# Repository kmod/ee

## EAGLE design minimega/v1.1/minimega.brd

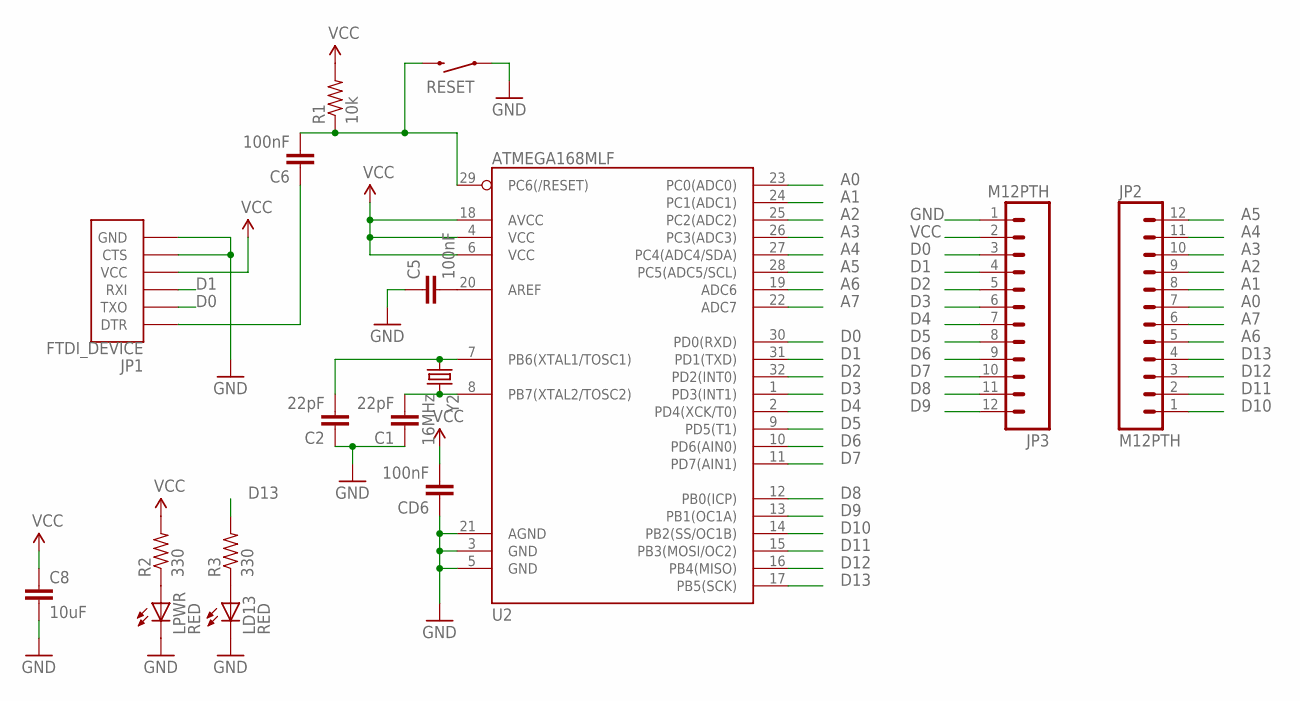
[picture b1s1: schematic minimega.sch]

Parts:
C1, C2: 22pF; 0402-CAP
C5, C6: 100nF; 0402-CAP
C8: 10uF; 0805
CD6: 100nF; 0402-CAP
JP1: FTDI_DEVICE; FTDI_DEVICE_SIDE
JP2, JP3: M12PTH; 1X12
LD13: RED; LED-0603
LPWR: RED; LED-0603
R1: 10k; 0603-RES
R2, R3: 330; 0603-RES
RESET: SWITCH-MOMENTARY-2PTH; TACTILE-PTH
U2: ATMEGA168MLF; MLF32
Y2: 16MHz; HC49UP

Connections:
A0: JP2.7, U2.23 (PC0(ADC0))
A1: JP2.8, U2.24 (PC1(ADC1))
A2: JP2.9, U2.25 (PC2(ADC2))
A3: JP2.10, U2.26 (PC3(ADC3))
A4: JP2.11, U2.27 (PC4(ADC4/SDA))
A5: JP2.12, U2.28 (PC5(ADC5/SCL))
A6: JP2.5, U2.19 (ADC6)
A7: JP2.6, U2.22 (ADC7)
D0: JP1.P$2 (TXO), JP3.3, U2.30 (PD0(RXD))
D1: JP1.P$3 (RXI), JP3.4, U2.31 (PD1(TXD))
D2: JP3.5, U2.32 (PD2(INT0))
D3: JP3.6, U2.1 (PD3(INT1))
D4: JP3.7, U2.2 (PD4(XCK/T0))
D5: JP3.8, U2.9 (PD5(T1))
D6: JP3.9, U2.10 (PD6(AIN0))
D7: JP3.10, U2.11 (PD7(AIN1))
D8: JP3.11, U2.12 (PB0(ICP))
D9: JP3.12, U2.13 (PB1(OC1A))
D10: JP2.1, U2.14 (PB2(SS/OC1B))
D11: JP2.2, U2.15 (PB3(MOSI/OC2))
D12: JP2.3, U2.16 (PB4(MISO))
D13: JP2.4, R3.2, U2.17 (PB5(SCK))
GND: C1.1, C2.1, C5.1, C8.2, CD6.1, JP1.P$5 (CTS), JP1.P$6 (GND), JP3.1, LD13.C, LPWR.C, RESET.1, U2.3 (GND), U2.5 (GND), U2.21 (AGND)
unnamed: LD13.A, R3.1
unnamed: C1.2, U2.8 (PB7(XTAL2/TOSC2)), Y2.2
unnamed: C2.2, U2.7 (PB6(XTAL1/TOSC1)), Y2.1
unnamed: C5.2, U2.20 (AREF)
unnamed: C6.2, R1.1, RESET.3 (2), U2.29 (PC6(/RESET))
unnamed: LPWR.A, R2.1
unnamed: C6.1, JP1.P$1 (DTR)
VCC: C8.1, CD6.2, JP1.P$4 (VCC), JP3.2, R1.2, R2.2, U2.4 (VCC), U2.6 (VCC), U2.18 (AVCC)

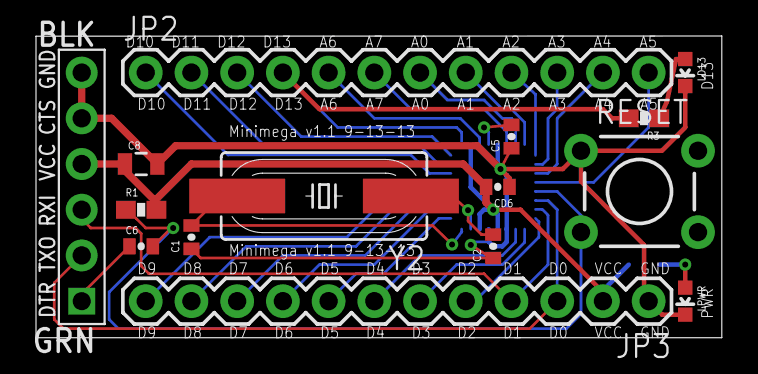
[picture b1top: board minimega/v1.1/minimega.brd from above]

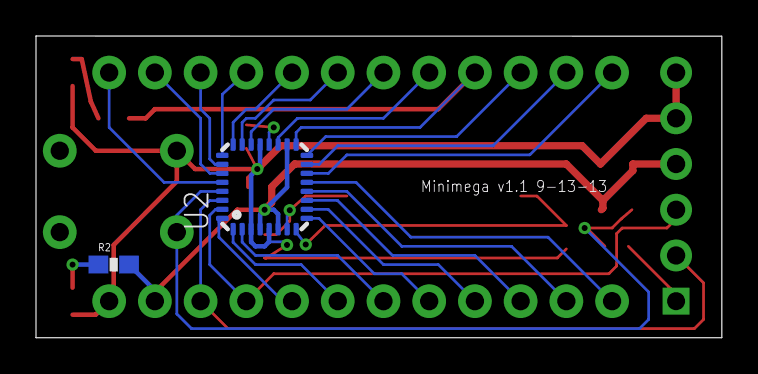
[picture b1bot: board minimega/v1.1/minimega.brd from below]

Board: 2 copper layers, 38.1 x 16.8 mm, 17 parts (2 on the bottom side), 31 nets.

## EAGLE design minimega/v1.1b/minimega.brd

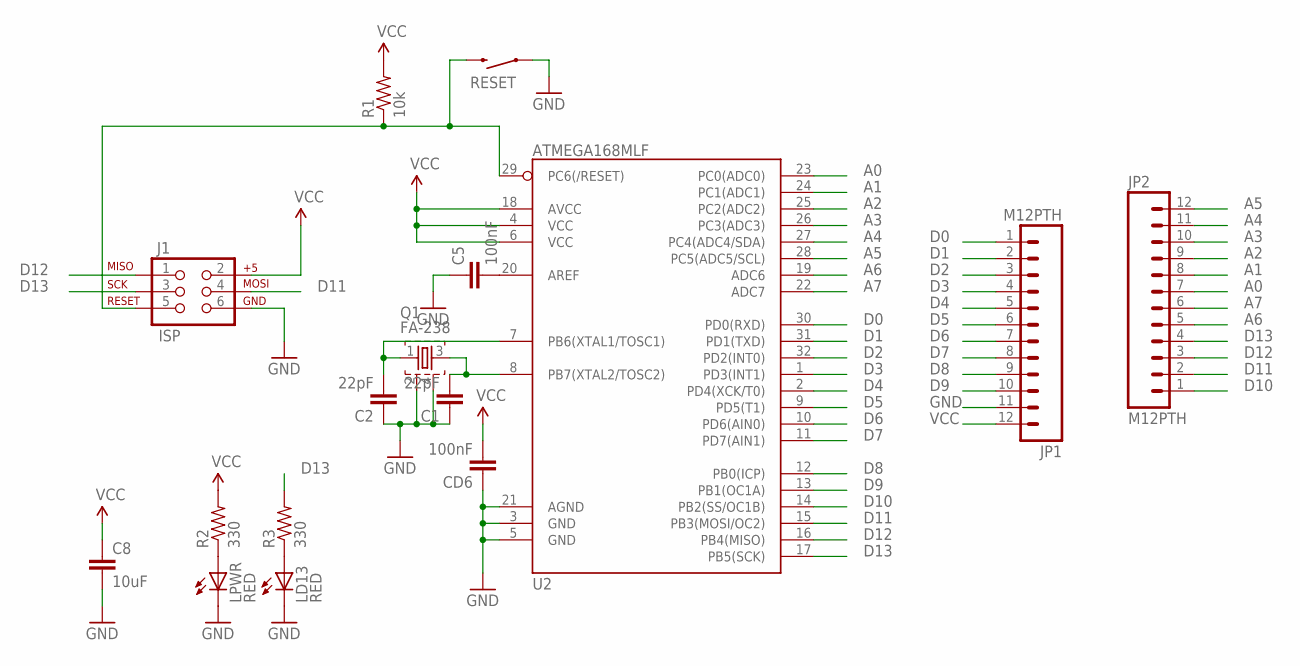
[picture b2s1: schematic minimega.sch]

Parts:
C1, C2: 22pF; 0402-CAP
C5: 100nF; 0402-CAP
C8: 10uF; 0805
CD6: 100nF; 0402-CAP
J1: ISP; 2X3
JP1, JP2: M12PTH; 1X12
LD13: RED; LED-0603
LPWR: RED; LED-0603
Q1: FA-238
R1: 10k; 0603-RES
R2, R3: 330; 0603-RES
RESET: SWITCH-MOMENTARY-2PTH; TACTILE-PTH
U2: ATMEGA168MLF; MLF32

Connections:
A0: JP2.7, U2.23 (PC0(ADC0))
A1: JP2.8, U2.24 (PC1(ADC1))
A2: JP2.9, U2.25 (PC2(ADC2))
A3: JP2.10, U2.26 (PC3(ADC3))
A4: JP2.11, U2.27 (PC4(ADC4/SDA))
A5: JP2.12, U2.28 (PC5(ADC5/SCL))
A6: JP2.5, U2.19 (ADC6)
A7: JP2.6, U2.22 (ADC7)
D0: JP1.1, U2.30 (PD0(RXD))
D1: JP1.2, U2.31 (PD1(TXD))
D2: JP1.3, U2.32 (PD2(INT0))
D3: JP1.4, U2.1 (PD3(INT1))
D4: JP1.5, U2.2 (PD4(XCK/T0))
D5: JP1.6, U2.9 (PD5(T1))
D6: JP1.7, U2.10 (PD6(AIN0))
D7: JP1.8, U2.11 (PD7(AIN1))
D8: JP1.9, U2.12 (PB0(ICP))
D9: JP1.10, U2.13 (PB1(OC1A))
D10: JP2.1, U2.14 (PB2(SS/OC1B))
D11: J1.4, JP2.2, U2.15 (PB3(MOSI/OC2))
D12: J1.1, JP2.3, U2.16 (PB4(MISO))
D13: J1.3, JP2.4, R3.2, U2.17 (PB5(SCK))
GND: C1.1, C2.1, C5.1, C8.2, CD6.1, J1.6, JP1.11, LD13.C, LPWR.C, Q1.2, Q1.4, RESET.1, U2.3 (GND), U2.5 (GND), U2.21 (AGND)
unnamed: LD13.A, R3.1
unnamed: C1.2, Q1.3, U2.8 (PB7(XTAL2/TOSC2))
unnamed: C2.2, Q1.1, U2.7 (PB6(XTAL1/TOSC1))
unnamed: C5.2, U2.20 (AREF)
unnamed: J1.5, R1.1, RESET.3 (2), U2.29 (PC6(/RESET))
unnamed: LPWR.A, R2.1
VCC: C8.1, CD6.2, J1.2, JP1.12, R1.2, R2.2, U2.4 (VCC), U2.6 (VCC), U2.18 (AVCC)

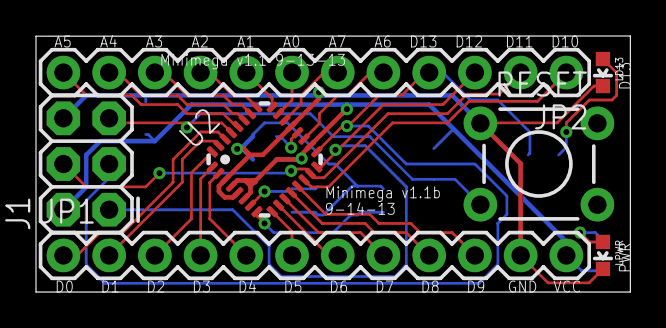
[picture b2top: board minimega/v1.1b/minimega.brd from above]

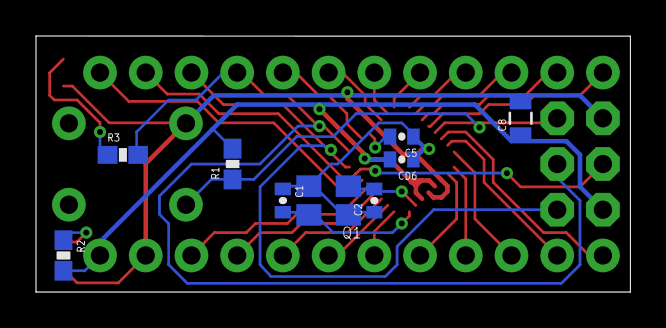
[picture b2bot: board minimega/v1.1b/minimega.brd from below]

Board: 2 copper layers, 33.0 x 14.2 mm, 16 parts (9 on the bottom side), 30 nets.

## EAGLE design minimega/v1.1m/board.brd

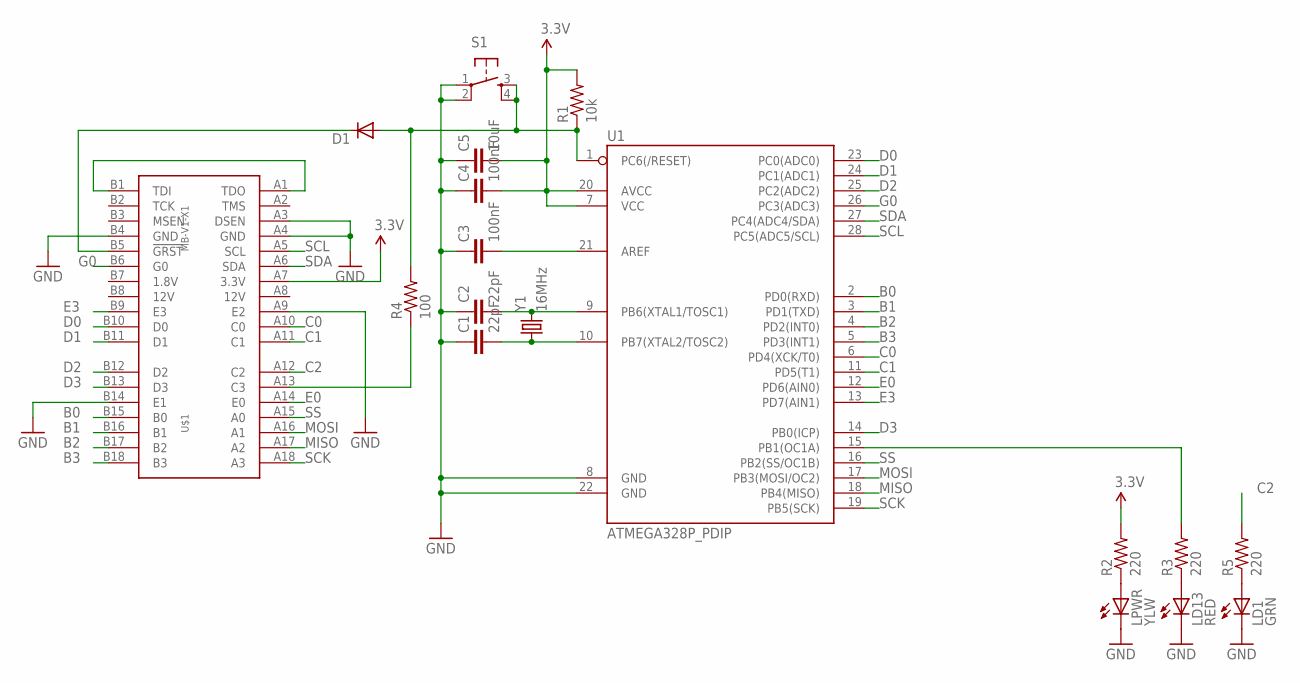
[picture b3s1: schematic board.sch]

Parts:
C1, C2: 22pF; 0402-CAP
C3, C4: 100nF; 0402-CAP
C5: 10uF; 0805
D1: DIODE1N4148; DIODE-1N4148
LD1: GRN; LED-0603
LD13: RED; LED-0603
LPWR: YLW; LED-0603
R1: 10k; 0603-RES
R2, R3, R5: 220; 0603-RES
R4: 100; 0603-RES
S1: TAC_SWITCHPTH; TACTILE-PTH
U1: ATMEGA328P_PDIP; DIL28-3
U$1: MB-V1-X1; PCIE-X1-EDGE
Y1: 16MHz; HC49US

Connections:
3.3V: C4.2, C5.2, R1.2, R2.2, U1.7 (VCC), U1.20 (AVCC), U$1.A7 (3.3V)
B0: U1.2 (PD0(RXD)), U$1.B15 (B0)
B1: U1.3 (PD1(TXD)), U$1.B16 (B1)
B2: U1.4 (PD2(INT0)), U$1.B17 (B2)
B3: U1.5 (PD3(INT1)), U$1.B18 (B3)
C0: U1.6 (PD4(XCK/T0)), U$1.A10 (C0)
C1: U1.11 (PD5(T1)), U$1.A11 (C1)
C2: R5.2, U$1.A12 (C2)
D0: U1.23 (PC0(ADC0)), U$1.B10 (D0)
D1: U1.24 (PC1(ADC1)), U$1.B11 (D1)
D2: U1.25 (PC2(ADC2)), U$1.B12 (D2)
D3: U1.14 (PB0(ICP)), U$1.B13 (D3)
E0: U1.12 (PD6(AIN0)), U$1.A14 (E0)
E3: U1.13 (PD7(AIN1)), U$1.B9 (E3)
G0: U1.26 (PC3(ADC3)), U$1.B6 (G0)
GND: C1.1, C2.1, C3.1, C4.1, C5.1, LD1.C, LD13.C, LPWR.C, S1.1, S1.2, U1.8 (GND), U1.22 (GND), U$1.A3 (DSEN), U$1.A4 (GND), U$1.A9 (E2), U$1.B4 (GND), U$1.B14 (E1)
MISO: U1.18 (PB4(MISO)), U$1.A17 (A2)
MOSI: U1.17 (PB3(MOSI/OC2)), U$1.A16 (A1)
unnamed: D1.C, U$1.B5 (!GRST)
unnamed: LD13.A, R3.1
unnamed: C2.2, U1.9 (PB6(XTAL1/TOSC1)), Y1.2
unnamed: C1.2, U1.10 (PB7(XTAL2/TOSC2)), Y1.1
unnamed: C3.2, U1.21 (AREF)
unnamed: U$1.A1 (TDO), U$1.B1 (TDI)
unnamed: LD1.A, R5.1
unnamed: R3.2, U1.15 (PB1(OC1A))
unnamed: R4.1, U$1.A13 (C3)
unnamed: LPWR.A, R2.1
RST: D1.A, R1.1, R4.2, S1.3, S1.4, U1.1 (PC6(/RESET))
SCK: U1.19 (PB5(SCK)), U$1.A18 (A3)
SCL: U1.28 (PC5(ADC5/SCL)), U$1.A5 (SCL)
SDA: U1.27 (PC4(ADC4/SDA)), U$1.A6 (SDA)
SS: U1.16 (PB2(SS/OC1B)), U$1.A15 (A0)

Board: 2 copper layers, 18 parts (0 on the bottom side), 33 nets, no tracks yet.

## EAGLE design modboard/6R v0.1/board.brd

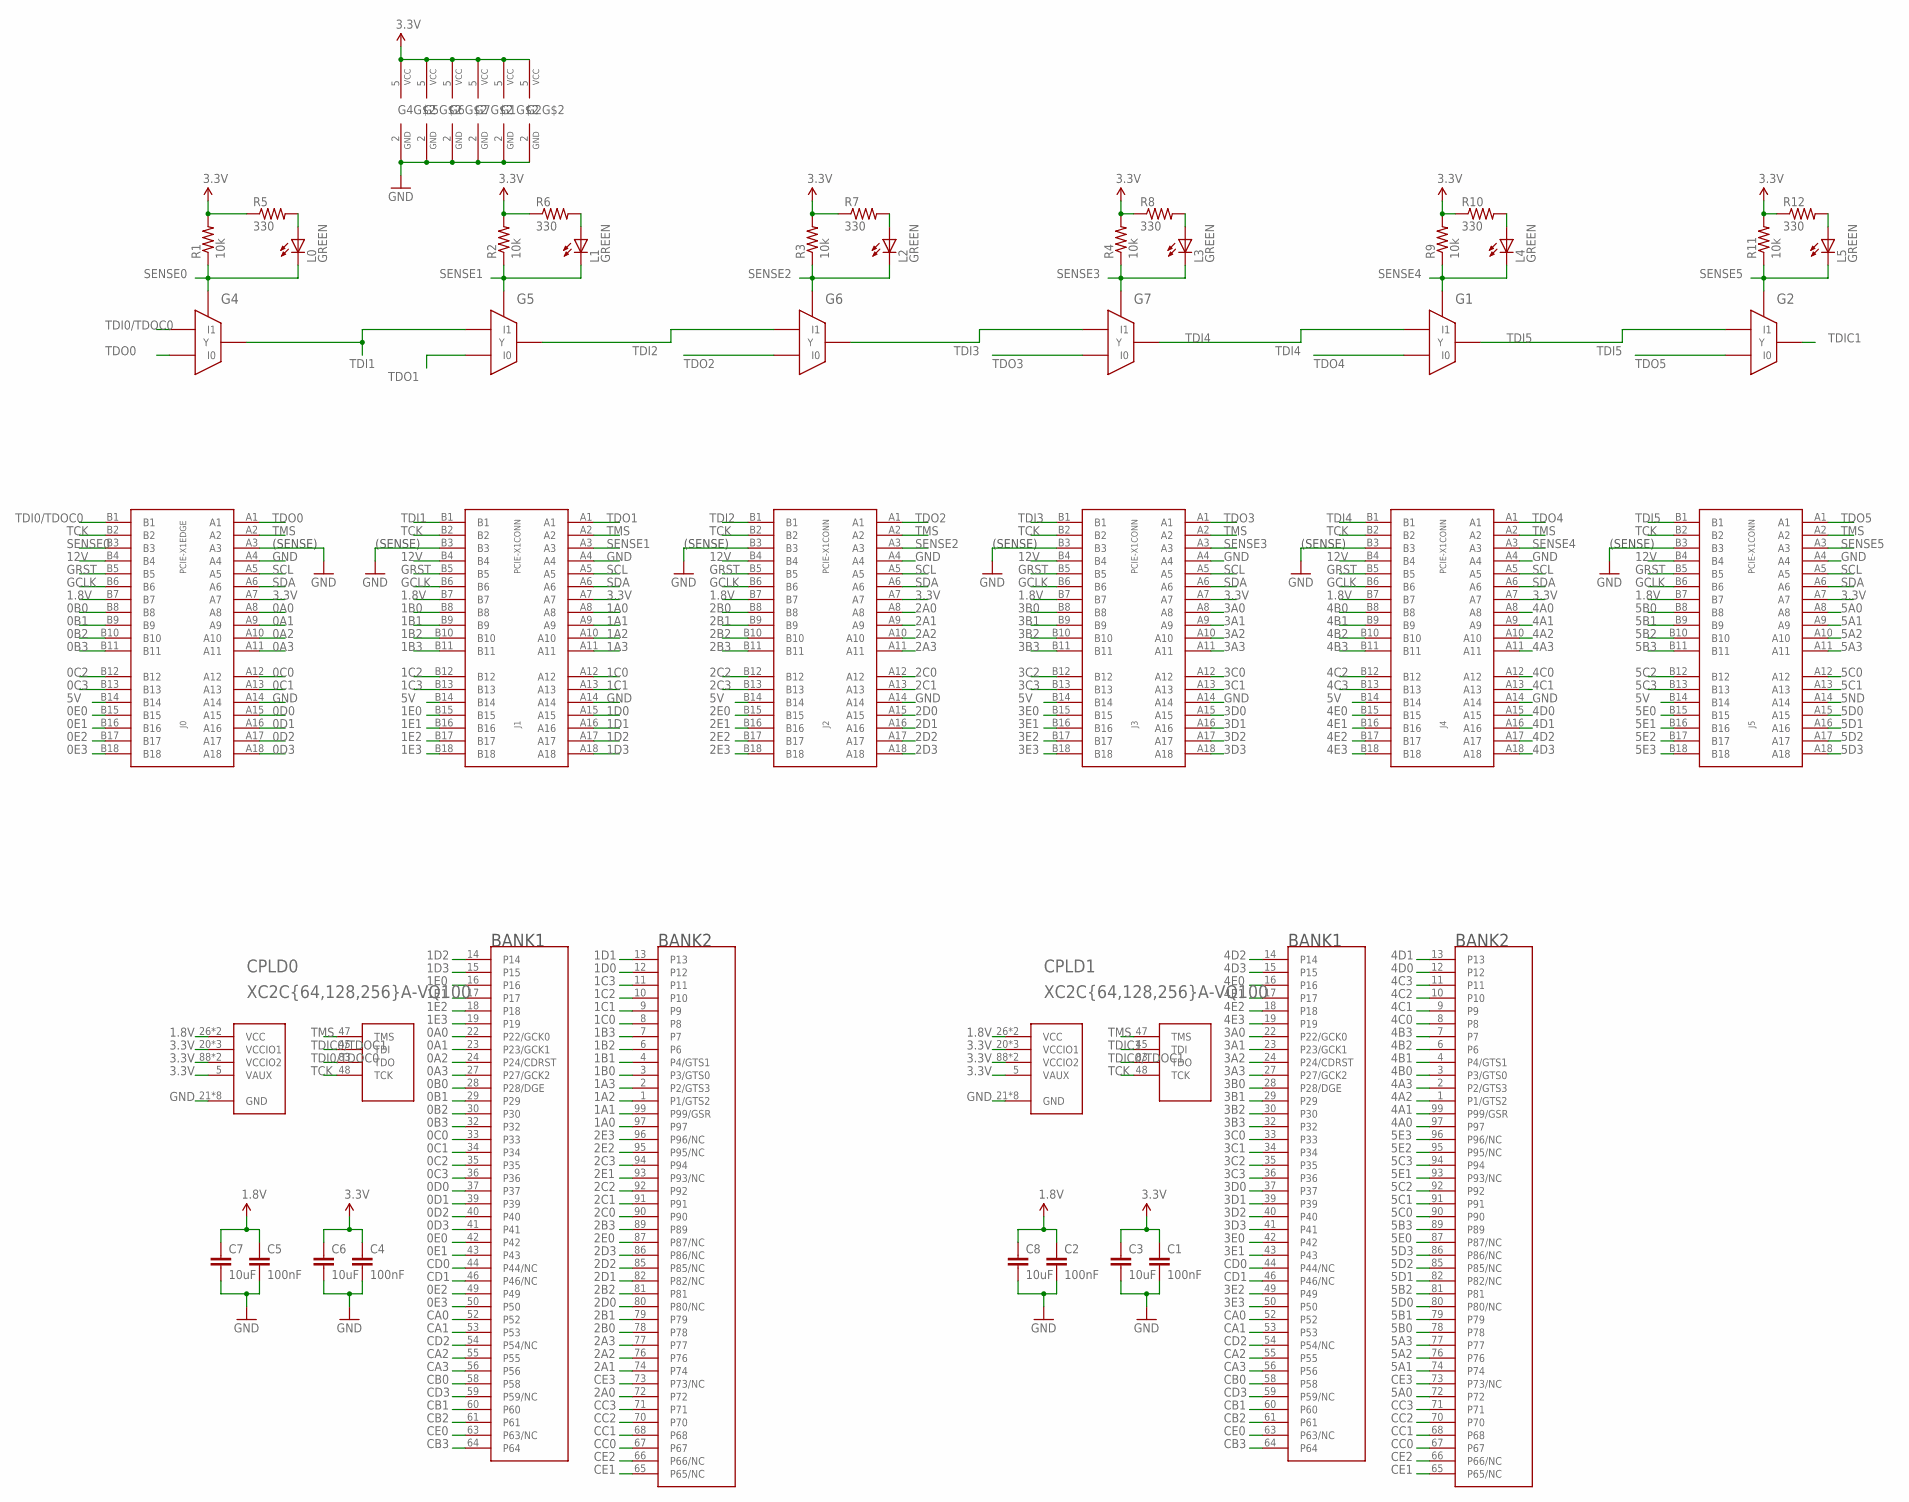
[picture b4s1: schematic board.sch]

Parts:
C1, C2, C4, C5: 100nF; 0402-CAP
C3, C6, C7, C8: 10uF; 0805
CPLD0, CPLD1: XC2C{64,128,256}A-VQ100; XILINX_TQ100
G1, G2, G4, G5, G6, G7: 74G157; SOT363
J0: PCIE-X1EDGE; PCIE-X1-EDGE
J1, J2, J3, J4, J5: PCIE-X1CONN; PCIE-X1-CONN
L0, L1, L2, L3, L4, L5: GREEN; 0603_LED
R1, R2, R3, R4, R9, R11: 10k; 0603-RES
R5, R6, R7, R8, R10, R12: 330; 0603-RES

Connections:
0A0: CPLD0.22 (P22/GCK0), J0.A8
0A1: CPLD0.23 (P23/GCK1), J0.A9
0A2: CPLD0.24 (P24/CDRST), J0.A10
0A3: CPLD0.27 (P27/GCK2), J0.A11
0B0: CPLD0.28 (P28/DGE), J0.B8
0B1: CPLD0.29, J0.B9
0B2: CPLD0.30, J0.B10
0B3: CPLD0.32, J0.B11
0C0: CPLD0.33, J0.A12
0C1: CPLD0.34, J0.A13
0C2: CPLD0.35, J0.B12
0C3: CPLD0.36, J0.B13
0D0: CPLD0.37, J0.A15
0D1: CPLD0.39, J0.A16
0D2: CPLD0.40, J0.A17
0D3: CPLD0.41, J0.A18
0E0: CPLD0.42, J0.B15
0E1: CPLD0.43, J0.B16
0E2: CPLD0.49, J0.B17
0E3: CPLD0.50, J0.B18
1.8V: C2.1, C5.1, C7.1, C8.1, CPLD0.26 (VCC), CPLD0.57 (VCC), CPLD1.26 (VCC), CPLD1.57 (VCC), J0.B7, J1.B7, J2.B7, J3.B7, J4.B7, J5.B7
1A0: CPLD0.97, J1.A8
1A1: CPLD0.99 (P99/GSR), J1.A9
1A2: CPLD0.1 (P1/GTS2), J1.A10
1A3: CPLD0.2 (P2/GTS3), J1.A11
1B0: CPLD0.3 (P3/GTS0), J1.B8
1B1: CPLD0.4 (P4/GTS1), J1.B9
1B2: CPLD0.6, J1.B10
1B3: CPLD0.7, J1.B11
1C0: CPLD0.8, J1.A12
1C1: CPLD0.9, J1.A13
1C2: CPLD0.10, J1.B12
1C3: CPLD0.11, J1.B13
1D0: CPLD0.12, J1.A15
1D1: CPLD0.13, J1.A16
1D2: CPLD0.14, J1.A17
1D3: CPLD0.15, J1.A18
1E0: CPLD0.16, J1.B15
1E1: CPLD0.17, J1.B16
1E2: CPLD0.18, J1.B17
1E3: CPLD0.19, J1.B18
2A0: CPLD0.72, J2.A8
2A1: CPLD0.74, J2.A9
2A2: CPLD0.76, J2.A10
2A3: CPLD0.77, J2.A11
2B0: CPLD0.78, J2.B8
2B1: CPLD0.79, J2.B9
2B2: CPLD0.81, J2.B10
2B3: CPLD0.89, J2.B11
2C0: CPLD0.90, J2.A12
2C1: CPLD0.91, J2.A13
2C2: CPLD0.92, J2.B12
2C3: CPLD0.94, J2.B13
2D0: CPLD0.80 (P80/NC), J2.A15
2D1: CPLD0.82 (P82/NC), J2.A16
2D2: CPLD0.85 (P85/NC), J2.A17
2D3: CPLD0.86 (P86/NC), J2.A18
2E0: CPLD0.87 (P87/NC), J2.B15
2E1: CPLD0.93 (P93/NC), J2.B16
2E2: CPLD0.95 (P95/NC), J2.B17
2E3: CPLD0.96 (P96/NC), J2.B18
3.3V: C1.1, C3.1, C4.1, C6.1, CPLD0.5 (VAUX), CPLD0.20 (VCCIO1), CPLD0.38 (VCCIO1), CPLD0.51 (VCCIO1), CPLD0.88 (VCCIO2), CPLD0.98 (VCCIO2), CPLD1.5 (VAUX), CPLD1.20 (VCCIO1), CPLD1.38 (VCCIO1), CPLD1.51 (VCCIO1), CPLD1.88 (VCCIO2), CPLD1.98 (VCCIO2), G1.5 (VCC), G2.5 (VCC), G4.5 (VCC), G5.5 (VCC), G6.5 (VCC), G7.5 (VCC), J0.A7, J1.A7, J2.A7, J3.A7, J4.A7, J5.A7, R1.2, R2.2, R3.2, R4.2, R5.1, R6.1, R7.1, R8.1, R9.2, R10.1, R11.2, R12.1
3A0: CPLD1.22 (P22/GCK0), J3.A8
3A1: CPLD1.23 (P23/GCK1), J3.A9
3A2: CPLD1.24 (P24/CDRST), J3.A10
3A3: CPLD1.27 (P27/GCK2), J3.A11
3B0: CPLD1.28 (P28/DGE), J3.B8
3B1: CPLD1.29, J3.B9
3B2: CPLD1.30, J3.B10
3B3: CPLD1.32, J3.B11
3C0: CPLD1.33, J3.A12
3C1: CPLD1.34, J3.A13
3C2: CPLD1.35, J3.B12
3C3: CPLD1.36, J3.B13
3D0: CPLD1.37, J3.A15
3D1: CPLD1.39, J3.A16
3D2: CPLD1.40, J3.A17
3D3: CPLD1.41, J3.A18
3E0: CPLD1.42, J3.B15
3E1: CPLD1.43, J3.B16
3E2: CPLD1.49, J3.B17
3E3: CPLD1.50, J3.B18
4A0: CPLD1.97, J4.A8
4A1: CPLD1.99 (P99/GSR), J4.A9
4A2: CPLD1.1 (P1/GTS2), J4.A10
4A3: CPLD1.2 (P2/GTS3), J4.A11
4B0: CPLD1.3 (P3/GTS0), J4.B8
4B1: CPLD1.4 (P4/GTS1), J4.B9
4B2: CPLD1.6, J4.B10
4B3: CPLD1.7, J4.B11
4C0: CPLD1.8, J4.A12
4C1: CPLD1.9, J4.A13
4C2: CPLD1.10, J4.B12
4C3: CPLD1.11, J4.B13
4D0: CPLD1.12, J4.A15
4D1: CPLD1.13, J4.A16
4D2: CPLD1.14, J4.A17
4D3: CPLD1.15, J4.A18
4E0: CPLD1.16, J4.B15
4E1: CPLD1.17, J4.B16
4E2: CPLD1.18, J4.B17
4E3: CPLD1.19, J4.B18
5A0: CPLD1.72, J5.A8
5A1: CPLD1.74, J5.A9
5A2: CPLD1.76, J5.A10
5A3: CPLD1.77, J5.A11
5B0: CPLD1.78, J5.B8
5B1: CPLD1.79, J5.B9
5B2: CPLD1.81, J5.B10
5B3: CPLD1.89, J5.B11
5C0: CPLD1.90, J5.A12
5C1: CPLD1.91, J5.A13
5C2: CPLD1.92, J5.B12
5C3: CPLD1.94, J5.B13
5D0: CPLD1.80 (P80/NC), J5.A15
5D1: CPLD1.82 (P82/NC), J5.A16
5D2: CPLD1.85 (P85/NC), J5.A17
5D3: CPLD1.86 (P86/NC), J5.A18
5E0: CPLD1.87 (P87/NC), J5.B15
5E1: CPLD1.93 (P93/NC), J5.B16
5E2: CPLD1.95 (P95/NC), J5.B17
5E3: CPLD1.96 (P96/NC), J5.B18
5ND: J5.A14
5V: J0.B14, J1.B14, J2.B14, J3.B14, J4.B14, J5.B14
12V: J0.B4, J1.B4, J2.B4, J3.B4, J4.B4, J5.B4
CA0: CPLD0.52, CPLD1.52
CA1: CPLD0.53, CPLD1.53
CA2: CPLD0.55, CPLD1.55
CA3: CPLD0.56, CPLD1.56
CB0: CPLD0.58, CPLD1.58
CB1: CPLD0.60, CPLD1.60
CB2: CPLD0.61, CPLD1.61
CB3: CPLD0.64, CPLD1.64
CC0: CPLD0.67, CPLD1.67
CC1: CPLD0.68, CPLD1.68
CC2: CPLD0.70, CPLD1.70
CC3: CPLD0.71, CPLD1.71
CD0: CPLD0.44 (P44/NC), CPLD1.44 (P44/NC)
CD1: CPLD0.46 (P46/NC), CPLD1.46 (P46/NC)
CD2: CPLD0.54 (P54/NC), CPLD1.54 (P54/NC)
CD3: CPLD0.59 (P59/NC), CPLD1.59 (P59/NC)
CE0: CPLD0.63 (P63/NC), CPLD1.63 (P63/NC)
CE1: CPLD0.65 (P65/NC), CPLD1.65 (P65/NC)
CE2: CPLD0.66 (P66/NC), CPLD1.66 (P66/NC)
CE3: CPLD0.73 (P73/NC), CPLD1.73 (P73/NC)
GCLK: J0.B6, J1.B6, J2.B6, J3.B6, J4.B6, J5.B6
GND: C1.2, C2.2, C3.2, C4.2, C5.2, C6.2, C7.2, C8.2, CPLD0.21 (GND), CPLD0.25 (GND), CPLD0.31 (GND), CPLD0.62 (GND), CPLD0.69 (GND), CPLD0.75 (GND), CPLD0.84 (GND), CPLD0.100 (GND), CPLD1.21 (GND), CPLD1.25 (GND), CPLD1.31 (GND), CPLD1.62 (GND), CPLD1.69 (GND), CPLD1.75 (GND), CPLD1.84 (GND), CPLD1.100 (GND), G1.2 (GND), G2.2 (GND), G4.2 (GND), G5.2 (GND), G6.2 (GND), G7.2 (GND), J0.A3, J0.A4, J0.A14, J1.A4, J1.A14, J1.B3, J2.A4, J2.A14, J2.B3, J3.A4, J3.A14, J3.B3, J4.A4, J4.A14, J4.B3, J5.A4, J5.B3
GRST: J0.B5, J1.B5, J2.B5, J3.B5, J4.B5, J5.B5
unnamed: L4.A, R10.2
unnamed: L5.A, R12.2
unnamed: L0.A, R5.2
unnamed: L1.A, R6.2
unnamed: L2.A, R7.2
unnamed: L3.A, R8.2
SCL: J0.A5, J1.A5, J2.A5, J3.A5, J4.A5, J5.A5
SDA: J0.A6, J1.A6, J2.A6, J3.A6, J4.A6, J5.A6
SENSE0: G4.6 (S), J0.B3, L0.C, R1.1
SENSE1: G5.6 (S), J1.A3, L1.C, R2.1
SENSE2: G6.6 (S), J2.A3, L2.C, R3.1
SENSE3: G7.6 (S), J3.A3, L3.C, R4.1
SENSE4: G1.6 (S), J4.A3, L4.C, R9.1
SENSE5: G2.6 (S), J5.A3, L5.C, R11.1
TCK: CPLD0.48 (TCK), CPLD1.48 (TCK), J0.B2, J1.B2, J2.B2, J3.B2, J4.B2, J5.B2
TDI0/TDOC0: CPLD0.83 (TDO), G4.1 (I1), J0.B1
TDI1: G4.4 (Y), G5.1 (I1), J1.B1
TDI2: G5.4 (Y), G6.1 (I1), J2.B1
TDI3: G6.4 (Y), G7.1 (I1), J3.B1
TDI4: G1.1 (I1), G7.4 (Y), J4.B1
TDI5: G1.4 (Y), G2.1 (I1), J5.B1
TDIC0/TDOC1: CPLD0.45 (TDI), CPLD1.83 (TDO)
TDIC1: CPLD1.45 (TDI), G2.4 (Y)
TDO0: G4.3 (I0), J0.A1
TDO1: G5.3 (I0), J1.A1
TDO2: G6.3 (I0), J2.A1
TDO3: G7.3 (I0), J3.A1
TDO4: G1.3 (I0), J4.A1
TDO5: G2.3 (I0), J5.A1
TMS: CPLD0.47 (TMS), CPLD1.47 (TMS), J0.A2, J1.A2, J2.A2, J3.A2, J4.A2, J5.A2

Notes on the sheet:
(SENSE)

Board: 2 copper layers, 40 parts (0 on the bottom side), 177 nets, no tracks yet.

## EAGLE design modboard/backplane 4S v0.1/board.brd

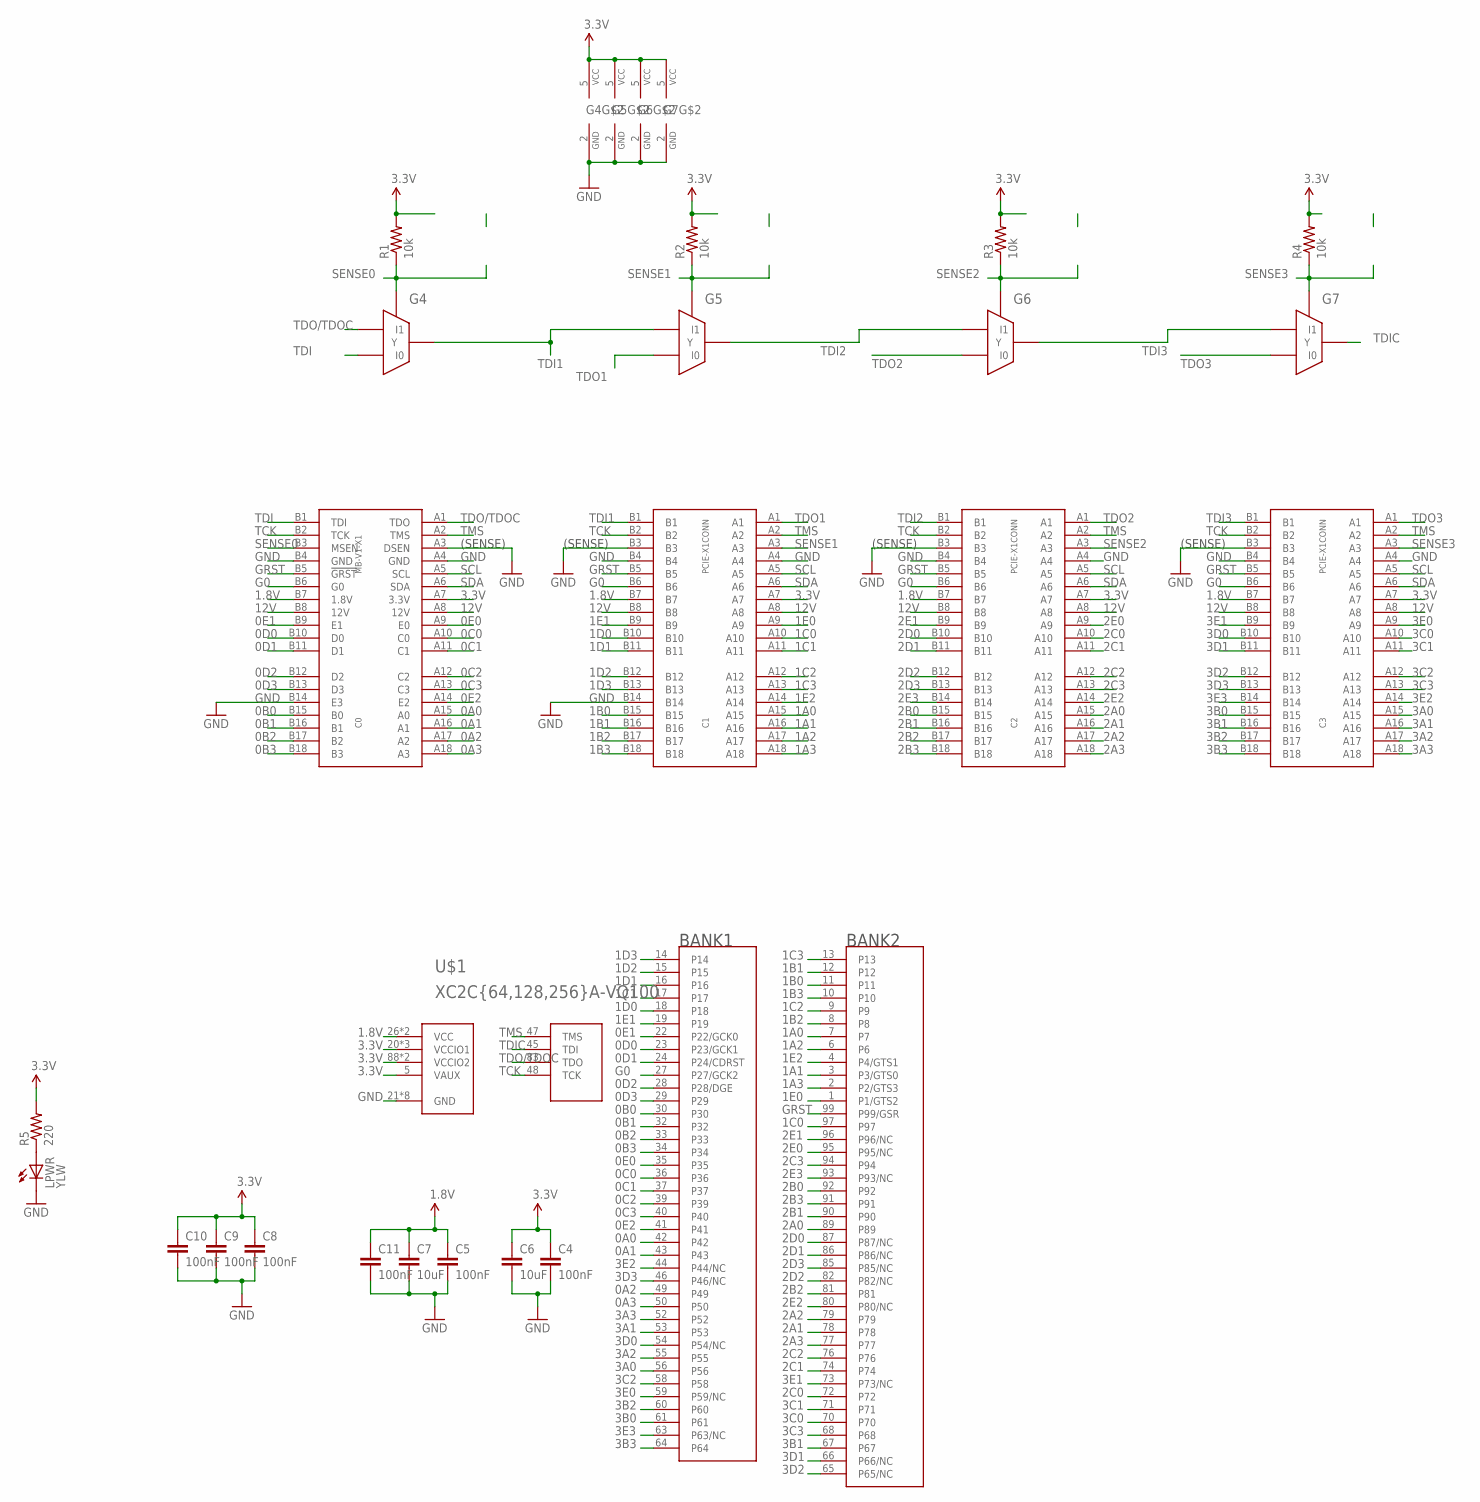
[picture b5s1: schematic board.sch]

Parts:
C0: MB-V1-X1; PCIE-X1-EDGE
C1, C2, C3: PCIE-X1CONN; PCIE-X1-CONN
C4, C5, C8, C9, C10, C11: 100nF; 0402-CAP
C6, C7: 10uF; 0805
G4, G5, G6, G7: 74G157; SOT363
LPWR: YLW; LED-0603
R1, R2, R3, R4: 10k; 0603-RES
R5: 220; 0603-RES
U$1: XC2C{64,128,256}A-VQ100; XILINX_TQ100

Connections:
0A0: C0.A15 (A0), U$1.42
0A1: C0.A16 (A1), U$1.43
0A2: C0.A17 (A2), U$1.49
0A3: C0.A18 (A3), U$1.50
0B0: C0.B15 (B0), U$1.30
0B1: C0.B16 (B1), U$1.32
0B2: C0.B17 (B2), U$1.33
0B3: C0.B18 (B3), U$1.34
0C0: C0.A10 (C0), U$1.36
0C1: C0.A11 (C1), U$1.37
0C2: C0.A12 (C2), U$1.39
0C3: C0.A13 (C3), U$1.40
0D0: C0.B10 (D0), U$1.23 (P23/GCK1)
0D1: C0.B11 (D1), U$1.24 (P24/CDRST)
0D2: C0.B12 (D2), U$1.28 (P28/DGE)
0D3: C0.B13 (D3), U$1.29
0E0: C0.A9 (E0), U$1.35
0E1: C0.B9 (E1), U$1.22 (P22/GCK0)
0E2: C0.A14 (E2), U$1.41
1.8V: C0.B7 (1.8V), C1.B7, C2.B7, C3.B7, C5.1, C7.1, C11.1, U$1.26 (VCC), U$1.57 (VCC)
1A0: C1.A15, U$1.7
1A1: C1.A16, U$1.3 (P3/GTS0)
1A2: C1.A17, U$1.6
1A3: C1.A18, U$1.2 (P2/GTS3)
1B0: C1.B15, U$1.11
1B1: C1.B16, U$1.12
1B2: C1.B17, U$1.8
1B3: C1.B18, U$1.10
1C0: C1.A10, U$1.97
1C1: C1.A11, U$1.17
1C2: C1.A12, U$1.9
1C3: C1.A13, U$1.13
1D0: C1.B10, U$1.18
1D1: C1.B11, U$1.16
1D2: C1.B12, U$1.15
1D3: C1.B13, U$1.14
1E0: C1.A9, U$1.1 (P1/GTS2)
1E1: C1.B9, U$1.19
1E2: C1.A14, U$1.4 (P4/GTS1)
2A0: C2.A15, U$1.89
2A1: C2.A16, U$1.78
2A2: C2.A17, U$1.79
2A3: C2.A18, U$1.77
2B0: C2.B15, U$1.92
2B1: C2.B16, U$1.90
2B2: C2.B17, U$1.81
2B3: C2.B18, U$1.91
2C0: C2.A10, U$1.72
2C1: C2.A11, U$1.74
2C2: C2.A12, U$1.76
2C3: C2.A13, U$1.94
2D0: C2.B10, U$1.87 (P87/NC)
2D1: C2.B11, U$1.86 (P86/NC)
2D2: C2.B12, U$1.82 (P82/NC)
2D3: C2.B13, U$1.85 (P85/NC)
2E0: C2.A9, U$1.95 (P95/NC)
2E1: C2.B9, U$1.96 (P96/NC)
2E2: C2.A14, U$1.80 (P80/NC)
2E3: C2.B14, U$1.93 (P93/NC)
3.3V: C0.A7 (3.3V), C1.A7, C2.A7, C3.A7, C4.1, C6.1, C8.1, C9.1, C10.1, G4.5 (VCC), G5.5 (VCC), G6.5 (VCC), G7.5 (VCC), R1.2, R2.2, R3.2, R4.2, R5.2, U$1.5 (VAUX), U$1.20 (VCCIO1), U$1.38 (VCCIO1), U$1.51 (VCCIO1), U$1.88 (VCCIO2), U$1.98 (VCCIO2)
3A0: C3.A15, U$1.56
3A1: C3.A16, U$1.53
3A2: C3.A17, U$1.55
3A3: C3.A18, U$1.52
3B0: C3.B15, U$1.61
3B1: C3.B16, U$1.67
3B2: C3.B17, U$1.60
3B3: C3.B18, U$1.64
3C0: C3.A10, U$1.70
3C1: C3.A11, U$1.71
3C2: C3.A12, U$1.58
3C3: C3.A13, U$1.68
3D0: C3.B10, U$1.54 (P54/NC)
3D1: C3.B11, U$1.66 (P66/NC)
3D2: C3.B12, U$1.65 (P65/NC)
3D3: C3.B13, U$1.46 (P46/NC)
3E0: C3.A9, U$1.59 (P59/NC)
3E1: C3.B9, U$1.73 (P73/NC)
3E2: C3.A14, U$1.44 (P44/NC)
3E3: C3.B14, U$1.63 (P63/NC)
12V: C0.A8 (12V), C0.B8 (12V), C1.A8, C1.B8, C2.A8, C2.B8, C3.A8, C3.B8
G0: C0.B6 (G0), C1.B6, C2.B6, C3.B6, U$1.27 (P27/GCK2)
GND: C0.A3 (DSEN), C0.A4 (GND), C0.B4 (GND), C0.B14 (E3), C1.A4, C1.B3, C1.B4, C1.B14, C2.A4, C2.B3, C2.B4, C3.A4, C3.B3, C3.B4, C4.2, C5.2, C6.2, C7.2, C8.2, C9.2, C10.2, C11.2, G4.2 (GND), G5.2 (GND), G6.2 (GND), G7.2 (GND), LPWR.C, U$1.21 (GND), U$1.25 (GND), U$1.31 (GND), U$1.62 (GND), U$1.69 (GND), U$1.75 (GND), U$1.84 (GND), U$1.100 (GND)
GRST: C0.B5 (!GRST), C1.B5, C2.B5, C3.B5, U$1.99 (P99/GSR)
unnamed: LPWR.A, R5.1
SCL: C0.A5 (SCL), C1.A5, C2.A5, C3.A5
SDA: C0.A6 (SDA), C1.A6, C2.A6, C3.A6
SENSE0: C0.B3 (MSEN), G4.6 (S), R1.1
SENSE1: C1.A3, G5.6 (S), R2.1
SENSE2: C2.A3, G6.6 (S), R3.1
SENSE3: C3.A3, G7.6 (S), R4.1
TCK: C0.B2 (TCK), C1.B2, C2.B2, C3.B2, U$1.48 (TCK)
TDI: C0.B1 (TDI), G4.3 (I0)
TDI1: C1.B1, G4.4 (Y), G5.1 (I1)
TDI2: C2.B1, G5.4 (Y), G6.1 (I1)
TDI3: C3.B1, G6.4 (Y), G7.1 (I1)
TDIC: G7.4 (Y), U$1.45 (TDI)
TDO1: C1.A1, G5.3 (I0)
TDO2: C2.A1, G6.3 (I0)
TDO3: C3.A1, G7.3 (I0)
TDO/TDOC: C0.A1 (TDO), G4.1 (I1), U$1.83 (TDO)
TMS: C0.A2 (TMS), C1.A2, C2.A2, C3.A2, U$1.47 (TMS)

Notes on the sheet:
(SENSE)

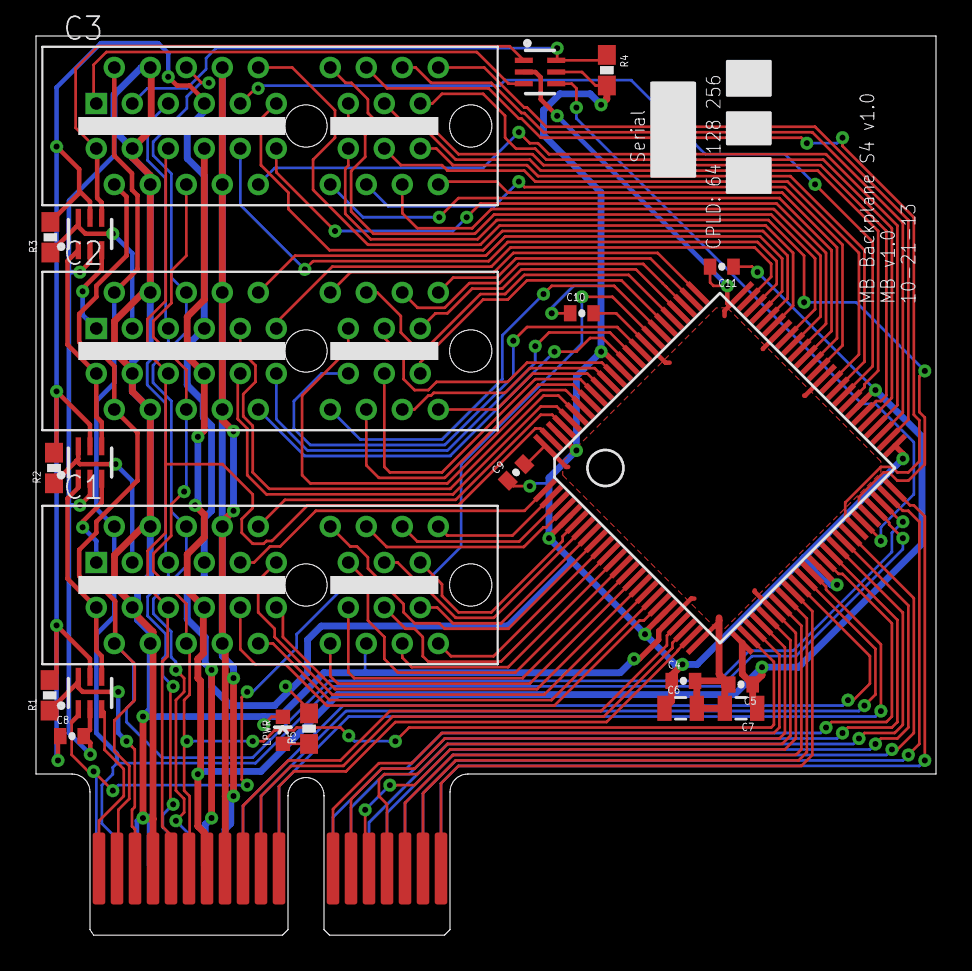
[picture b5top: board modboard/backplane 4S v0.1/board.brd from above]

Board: 2 copper layers, 50.0 x 50.0 mm, 23 parts (0 on the bottom side), 102 nets.

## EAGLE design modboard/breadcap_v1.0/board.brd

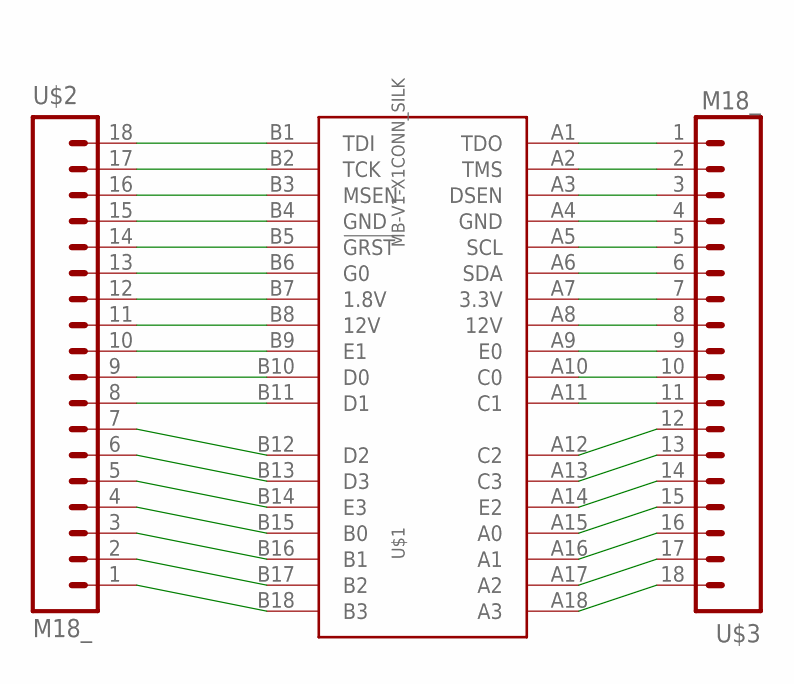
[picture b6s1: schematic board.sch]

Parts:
U$1: MB-V1-X1CONN_SILK; MB-V1-X1-CONN
U$2, U$3: M18_; 1X18

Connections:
1.8V: U$1.B7 (1.8V), U$2.12
3.3V: U$1.A7 (3.3V), U$3.7
12V: U$1.A8 (12V), U$1.B8 (12V), U$2.11, U$3.8
!GRST: U$1.B5 (!GRST), U$2.14
A0: U$1.A15 (A0), U$3.15
A1: U$1.A16 (A1), U$3.16
A2: U$1.A17 (A2), U$3.17
A3: U$1.A18 (A3), U$3.18
B0: U$1.B15 (B0), U$2.4
B1: U$1.B16 (B1), U$2.3
B2: U$1.B17 (B2), U$2.2
B3: U$1.B18 (B3), U$2.1
C0: U$1.A10 (C0), U$3.10
C1: U$1.A11 (C1), U$3.11
C2: U$1.A12 (C2), U$3.12
C3: U$1.A13 (C3), U$3.13
D0: U$1.B10 (D0), U$2.9
D1: U$1.B11 (D1), U$2.8
D2: U$1.B12 (D2), U$2.7
D3: U$1.B13 (D3), U$2.6
DSEN: U$1.A3 (DSEN), U$3.3
E0: U$1.A9 (E0), U$3.9
E1: U$1.B9 (E1), U$2.10
E2: U$1.A14 (E2), U$3.14
E3: U$1.B14 (E3), U$2.5
G0: U$1.B6 (G0), U$2.13
GND: U$1.A4 (GND), U$1.B4 (GND), U$2.15, U$3.4
MSEN: U$1.B3 (MSEN), U$2.16
SCL: U$1.A5 (SCL), U$3.5
SDA: U$1.A6 (SDA), U$3.6
TCK: U$1.B2 (TCK), U$2.17
TD0: U$1.A1 (TDO), U$3.1
TDI: U$1.B1 (TDI), U$2.18
TMS: U$1.A2 (TMS), U$3.2

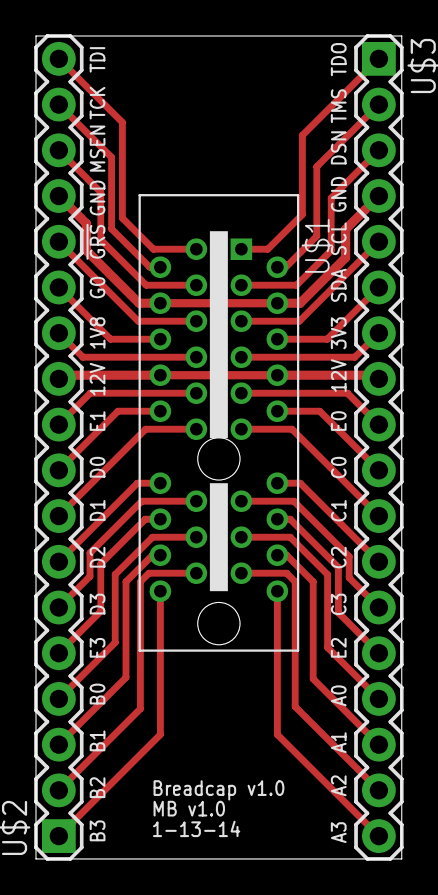
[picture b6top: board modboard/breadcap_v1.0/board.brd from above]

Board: 2 copper layers, 20.3 x 45.7 mm, 3 parts (0 on the bottom side), 34 nets.

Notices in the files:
parts and their libraries:
SparkFun-DigitalIC: Licensing: CC v3.0 Share-Alike You are welcome to use this library for commercial purposes.
SparkFun-DiscreteSemi: Licensing: Creative Commons ShareAlike 4.0 International - https://creativecommons.org/licenses/by-sa/4.0
